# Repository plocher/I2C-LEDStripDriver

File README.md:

# I2C-LEDStripDriver
## License: CERN Open Hardware Licence v1.2

I2C LED Strip Driver based on a PCA9685 

The PCA9685 is an I2C-bus controlled 16-channel LED controller optimized for Red/Green/Blue/Amber (RGBA) color backlighting applications.
Each LED output has its own 12-bit resolution (4096 steps) fixed frequency individual PWM controller

This design drives 2x RGB LED strips and 2x "white" strips - one set for backdrop lighting (dawn and dusk sunsets...) and the other for overhead (sunlight) valence illumination.

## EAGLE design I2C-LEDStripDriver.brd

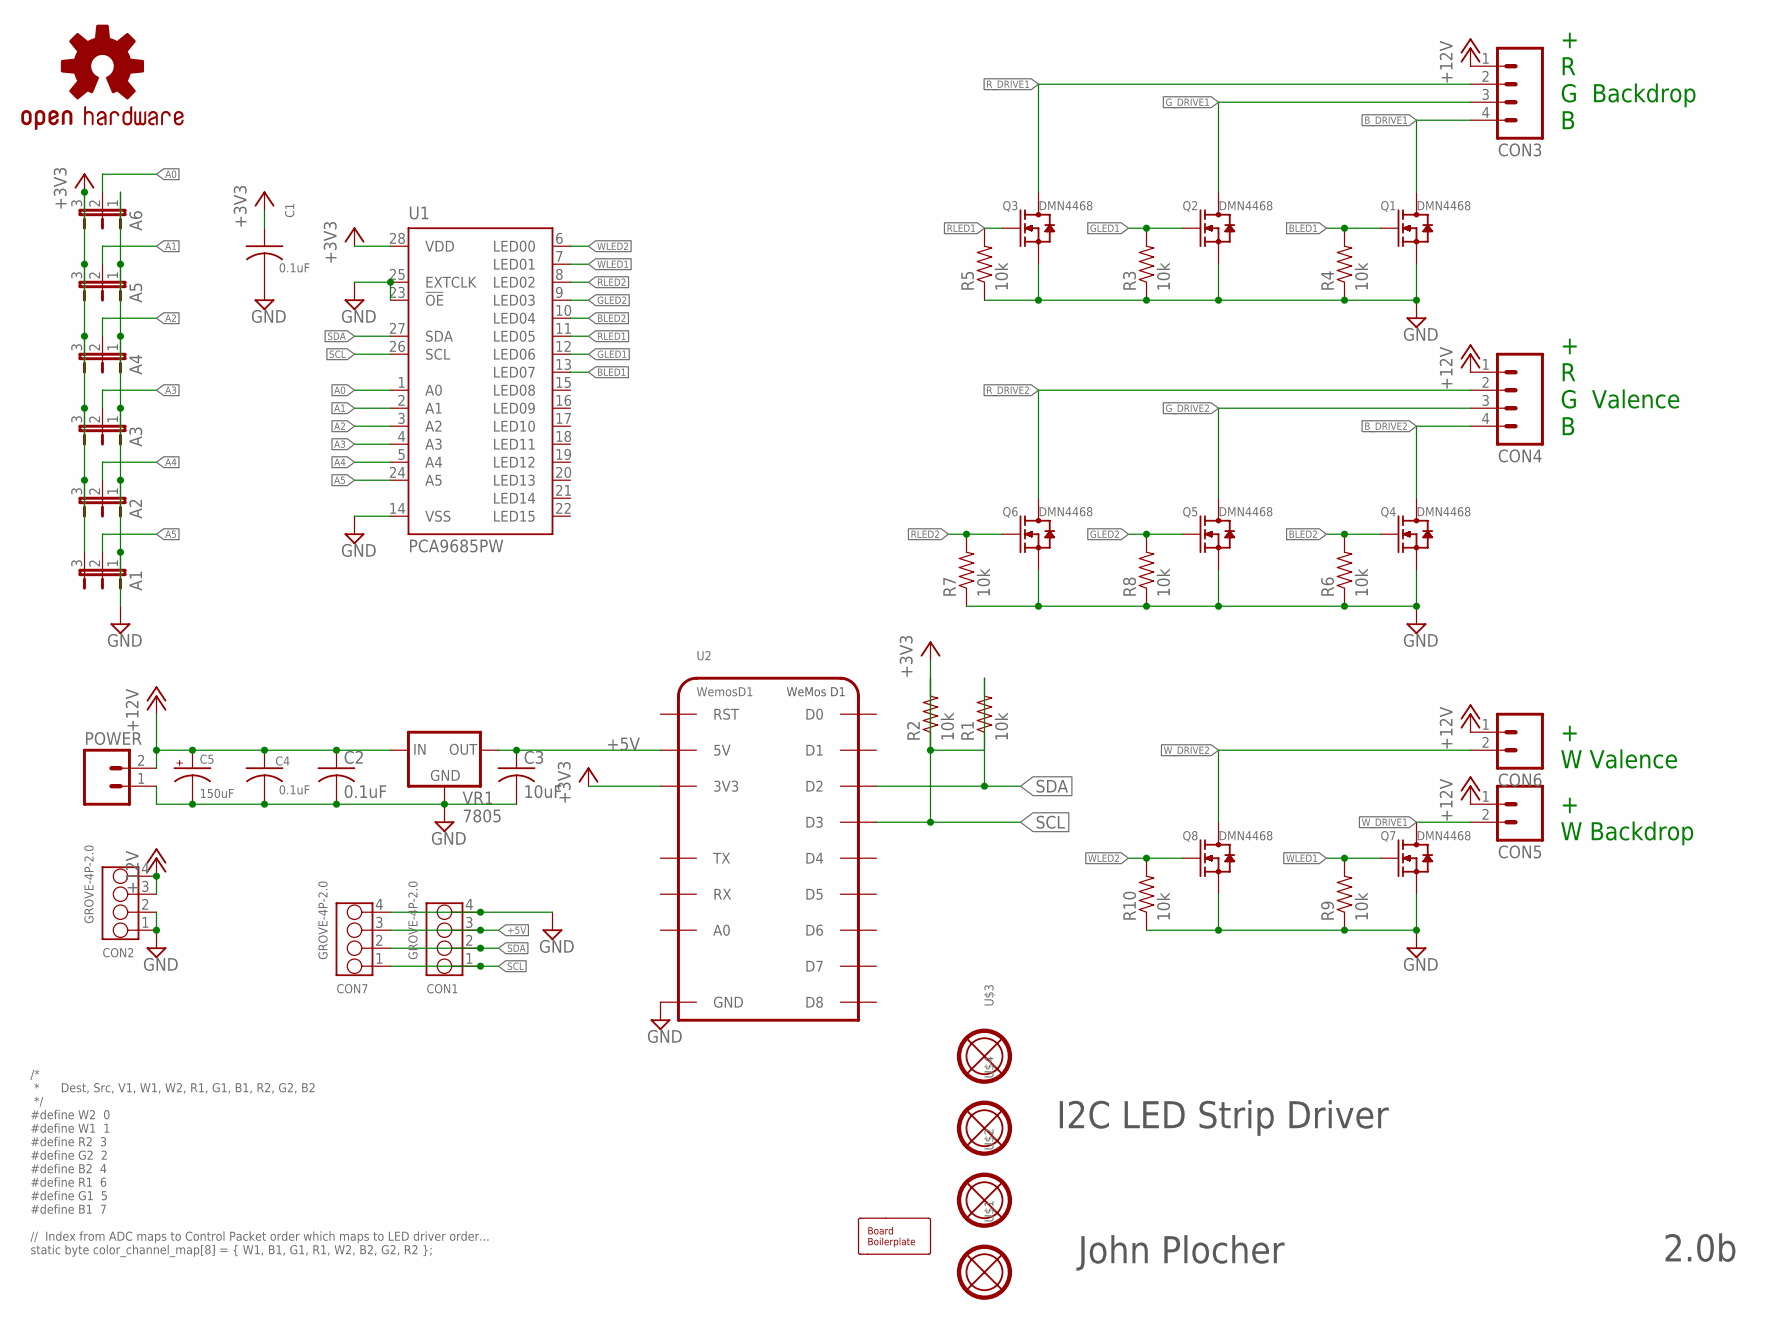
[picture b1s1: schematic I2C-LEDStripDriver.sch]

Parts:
A1, A2, A3, A4, A5, A6: JUMPER-3PTH-LOCK; 1X03
BOARD1: BOARD80X100-TEMPLATE; BOARD-10X8-TEMPLATE
C1, C4: 0.1uF; 0603-CAP
C2: 0.1uF; 0805-CAP
C3: 10uF; 0805-CAP
C5: 150uF; 0810-CAP
CON1, CON2, CON7: GROVE-4P-2.0; 4P-2.0
CON3, CON4: CONNECTOR-M045.08; MSTBA4
CON5, CON6: CONNECTOR-M02MSTBA2; MSTBA2
OSHW1: OSHW-LOGOL; OSHW-LOGO-L
POWER: CONNECTOR-M02MSTBA2; MSTBA2
Q1, Q2, Q3, Q4, Q5, Q6, Q7, Q8: DMN4468; SO08
R1, R2, R3, R4, R5, R6, R7, R8, R9, R10: 10k; 0603-RES
U1: PCA9685PW; TSSOP28
U2: WemosD1; WEMOS-D1
U$1, U$2, U$3, U$4: MOUNTINGHOLE
VR1: 7805; TO-252

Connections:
+3V3: A1.3, A2.3, A3.3, A4.3, A5.3, A6.3, C1.1, R1.1, R2.1, U1.28 (VDD), U2.3V3
+5V: C3.1, CON1.3, CON7.3, U2.5V, VR1.3 (OUT)
+12V: C2.1, C4.1, C5.+, CON2.3, CON2.4, CON3.1, CON4.1, CON5.1 (A), CON6.1 (A), POWER.2 (B), VR1.1 (IN)
A0: A6.2, U1.1 (A0)
A1: A5.2, U1.2 (A1)
A2: A4.2, U1.3 (A2)
A3: A3.2, U1.4 (A3)
A4: A2.2, U1.5 (A4)
A5: A1.2, U1.24 (A5)
BLED1: Q1.4 (G), R4.2, U1.13 (LED07)
BLED2: Q4.4 (G), R6.2, U1.10 (LED04)
B_DRIVE1: CON3.4, Q1.5 (D), Q1.6 (D), Q1.7 (D), Q1.8 (D)
B_DRIVE2: CON4.4, Q4.5 (D), Q4.6 (D), Q4.7 (D), Q4.8 (D)
GLED1: Q2.4 (G), R3.2, U1.12 (LED06)
GLED2: Q5.4 (G), R8.2, U1.9 (LED03)
GND: A1.1, A2.1, A3.1, A4.1, A5.1, A6.1, C1.2, C2.2, C3.2, C4.2, C5.-, CON1.4, CON2.1, CON2.2, CON7.4, POWER.1 (A), Q1.1 (S), Q1.2 (S), Q1.3 (S), Q2.1 (S), Q2.2 (S), Q2.3 (S), Q3.1 (S), Q3.2 (S), Q3.3 (S), Q4.1 (S), Q4.2 (S), Q4.3 (S), Q5.1 (S), Q5.2 (S), Q5.3 (S), Q6.1 (S), Q6.2 (S), Q6.3 (S), Q7.1 (S), Q7.2 (S), Q7.3 (S), Q8.1 (S), Q8.2 (S), Q8.3 (S), R3.1, R4.1, R5.1, R6.1, R7.1, R8.1, R9.1, R10.1, U1.14 (VSS), U1.23 (!OE), U1.25 (EXTCLK), U2.GND, VR1.2 (GND)
G_DRIVE1: CON3.3, Q2.5 (D), Q2.6 (D), Q2.7 (D), Q2.8 (D)
G_DRIVE2: CON4.3, Q5.5 (D), Q5.6 (D), Q5.7 (D), Q5.8 (D)
RLED1: Q3.4 (G), R5.2, U1.11 (LED05)
RLED2: Q6.4 (G), R7.2, U1.8 (LED02)
R_DRIVE1: CON3.2, Q3.5 (D), Q3.6 (D), Q3.7 (D), Q3.8 (D)
R_DRIVE2: CON4.2, Q6.5 (D), Q6.6 (D), Q6.7 (D), Q6.8 (D)
SCL: CON1.1, CON7.1, R2.2, U1.26 (SCL), U2.D3
SDA: CON1.2, CON7.2, R1.2, U1.27 (SDA), U2.D2
WLED1: Q7.4 (G), R9.2, U1.7 (LED01)
WLED2: Q8.4 (G), R10.2, U1.6 (LED00)
W_DRIVE1: CON5.2 (B), Q7.5 (D), Q7.6 (D), Q7.7 (D), Q7.8 (D)
W_DRIVE2: CON6.2 (B), Q8.5 (D), Q8.6 (D), Q8.7 (D), Q8.8 (D)

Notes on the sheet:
I2C LED Strip Driver
John Plocher
2.0b
+ R G Backdrop B
+ R G Valence B
+ W Valence
+ W Backdrop
/* * Dest, Src, V1, W1, W2, R1, G1, B1, R2, G2, B2 */ #define W2 0 #define W1 1 #define R2 3 #define G2 2 #define B2 4 #define R1 6 #define G1 5 #define B1 7 // Index from ADC maps to Control Packet order which maps to LED driver order... static byte color_channel_map[8] = { W1, B1, G1, R1, W2, B2,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

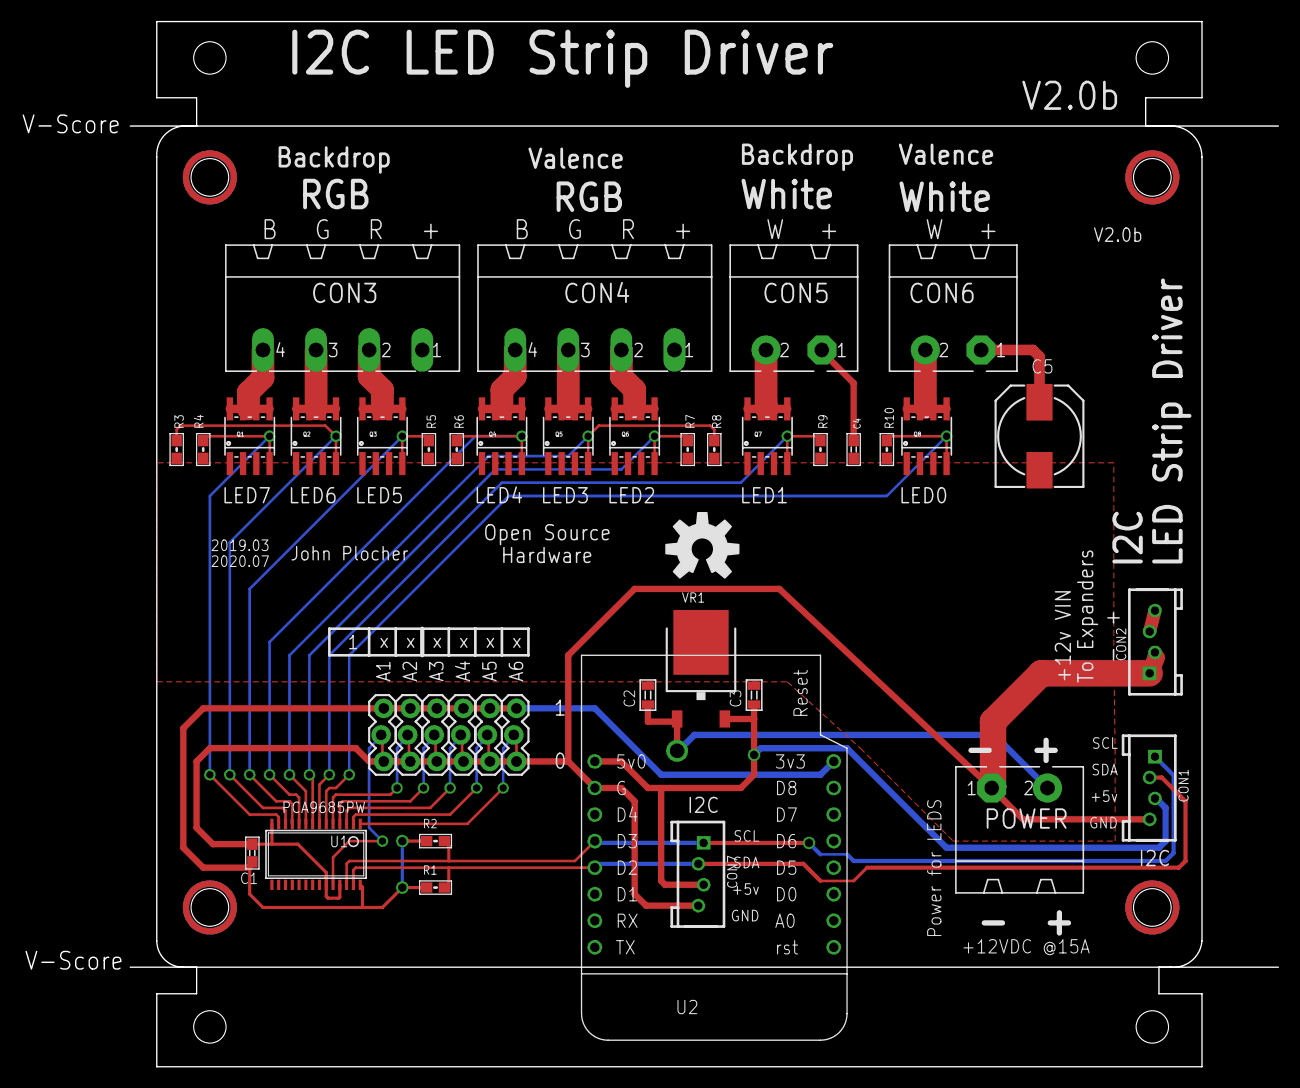
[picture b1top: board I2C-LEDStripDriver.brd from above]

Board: 2 copper layers, 120.3 x 100.0 mm, 46 parts (0 on the bottom side), 28 nets.

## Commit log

2019-11-25 WiFi, too
2019-12-07 added graphic
2020-05-04 updated tags
2020-07-27 default address (0) and silkscreen updates
